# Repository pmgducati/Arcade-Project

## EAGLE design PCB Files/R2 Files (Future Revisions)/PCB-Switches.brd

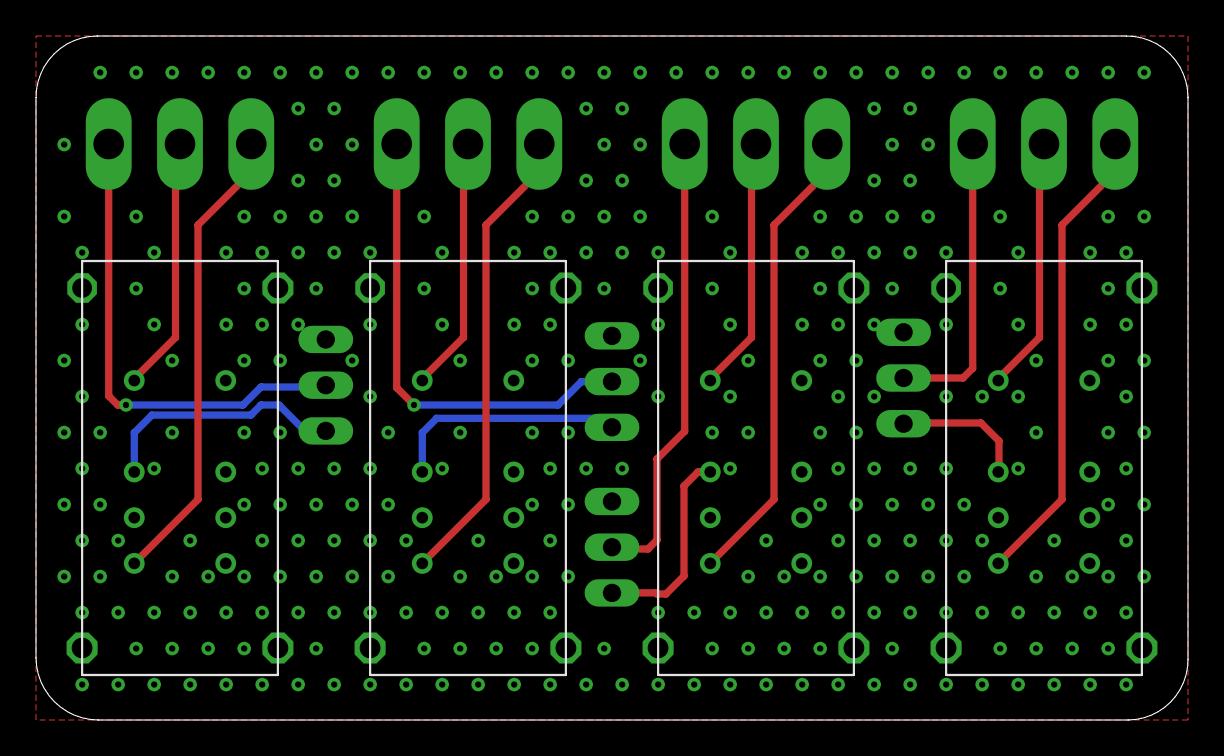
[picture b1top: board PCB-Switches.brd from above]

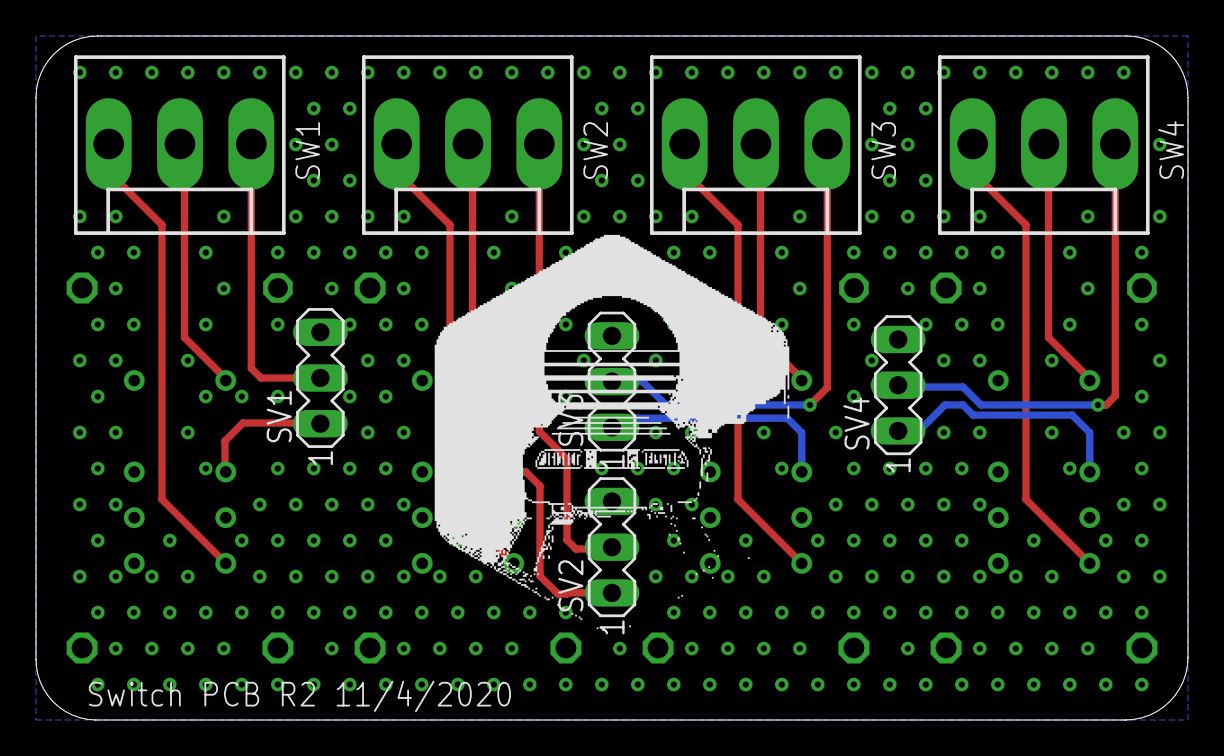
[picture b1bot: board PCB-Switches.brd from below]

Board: 2 copper layers, 64.0 x 38.0 mm, 12 parts (8 on the bottom side), 17 nets.

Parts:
SV1, SV2, SV3, SV4: MA03-1
SW1, SW2, SW3, SW4: KK-156-3
U$1, U$2, U$3, U$4: ARCADESWITCH

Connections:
GND: SV1.3, SV2.3, SV3.3, SV4.3
SW1A: SW1.2, U$1.LN1
SW1B: SW1.3, U$1.LN2
SW1J: SV1.1, U$1.LI
SW1P: SV1.2, SW1.1
SW2A: SW2.2, U$2.LN1
SW2B: SW2.3, U$2.LN2
SW2J: SV2.1, U$2.LI
SW2P: SV2.2, SW2.1
SW3A: SW3.2, U$3.LN1
SW3B: SW3.3, U$3.LN2
SW3J: SV3.1, U$3.LI
SW3P: SV3.2, SW3.1
SW4A: SW4.2, U$4.LN1
SW4B: SW4.3, U$4.LN2
SW4J: SV4.1, U$4.LI
SW4P: SV4.2, SW4.1
